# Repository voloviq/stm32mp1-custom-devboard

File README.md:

# stm32mp1-visionsom-custom-devboard
Custom development board for is located in two separated branch for stm32mp1-visionsom from Somlabs and osd32mp1 from Octavo Systems.

Development boards are created in KiCad.

Boards supported with DSI Display with touchscreen, arduino header, power supply, ethernet and usb.

Board 3D View

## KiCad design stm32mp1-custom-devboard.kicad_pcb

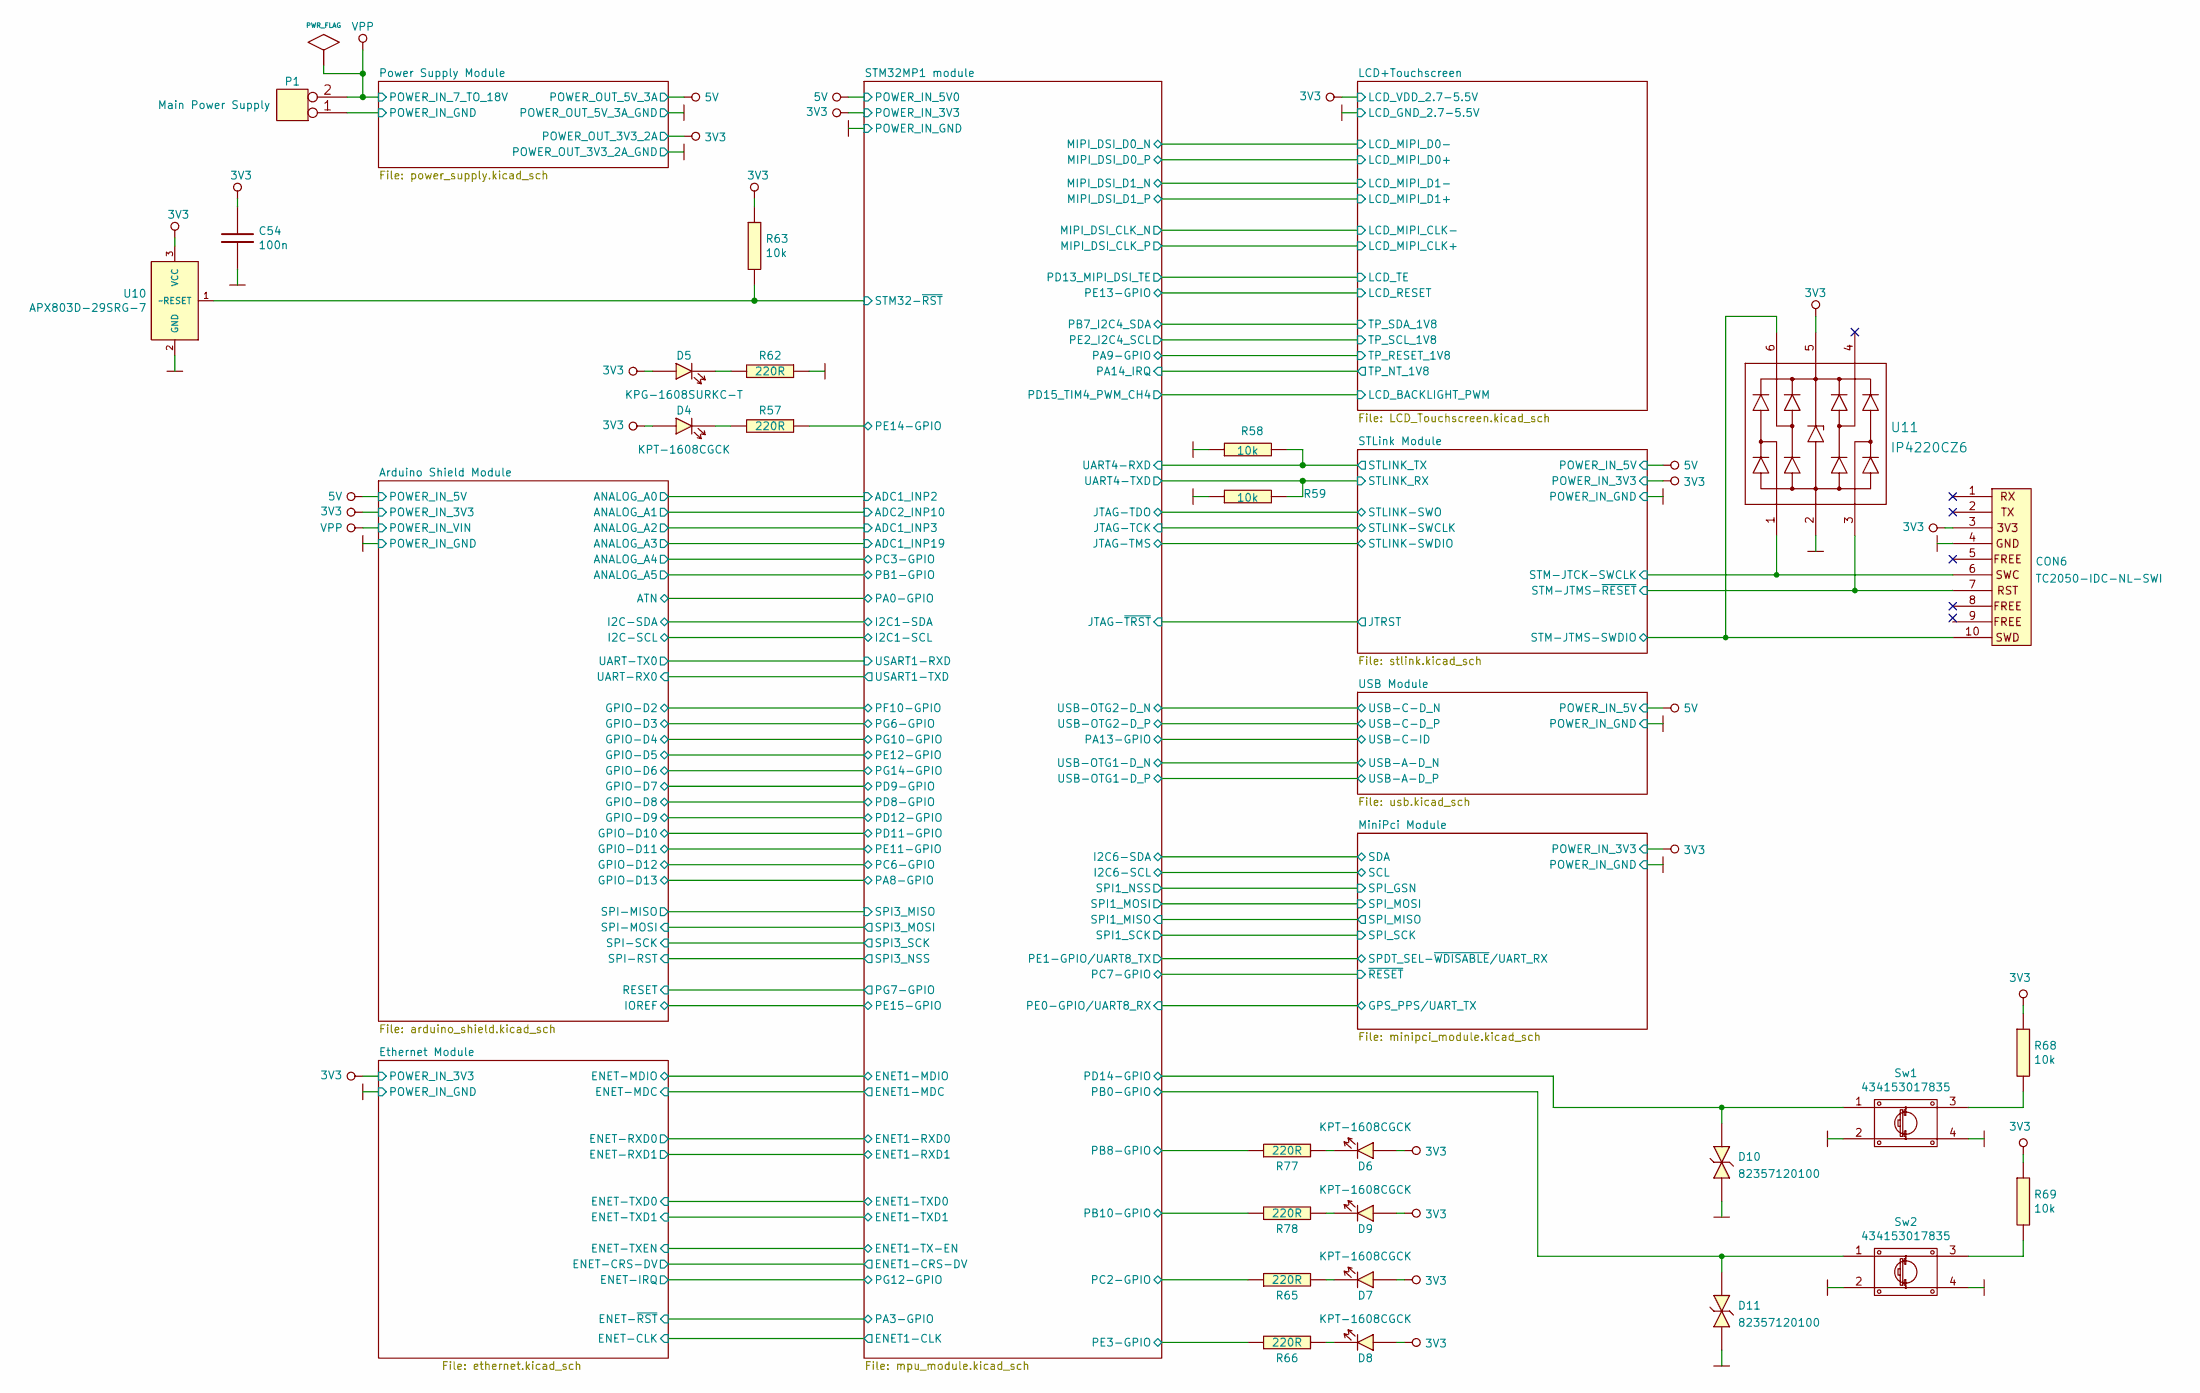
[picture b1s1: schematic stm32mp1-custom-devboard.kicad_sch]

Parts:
C54: 100n; 100nF_0603; Manufacturer Part Number CL10B104JB8NNNC
CON6: TC2050-IDC-NL-SWI; TC2050-IDC-NL
D4, D6, D7, D8, D9: KPT-1608CGCK; LED_KPT-1608CGCK; Manufacturer Part Number KP-1608CGCK; LCSC Part # (optional) C192316
D5: KPG-1608SURKC-T; LED_KPG-1608SURKC-T; Manufacturer Part Number KPG-1608SURKC-T; LCSC Part # (optional) C192315
D10, D11: 82357120100; Manufacturer Part Number 82357120100; LCSC Part #(optional) C39109
P1: Main Power Supply; 2060-452_998-404; Manufacturer Part Number 2060-452/998-404
R57, R62, R65, R66, R77, R78: 220R; 220R_0603; Manufacturer Part Number CQ03SAF2203T5E; LCSC Part #(optional) C103414
R58, R59, R63, R68, R69: 10k; 10k_0603; Manufacturer Part Number 0603SAJ0103T5E
Sw1, Sw2: 434153017835; Manufacturer Part Number 434153017835
U10: APX803D-29SRG-7; Manufacturer Part Number APX803D-29SRG-7; LCSC Part #(optional) C460556
U11: IP4220CZ6; IP4220CZ6_SOT457; Manufacturer Part Number IP4220CZ6.125; LCSC Part #(optional) C2687127

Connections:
3V3: C54.1, CON6.3, D4.1 (A), D5.1 (A), D6.1 (A), D7.1 (A), D8.1 (A), D9.1 (A), R63.1, R68.1, R69.1, U10.3 (VCC), U11.5 (Vp); also elsewhere on the board
/STLink Module/STLINK_RX: R59.2; also elsewhere on the board
/STLink Module/STLINK_TX: R58.2; also elsewhere on the board
/STLink Module/STM-JTCK-SWCLK: CON6.6, U11.1 (I/O1); also elsewhere on the board
/STLink Module/STM-JTMS-SWDIO: CON6.10, U11.6 (I/O4); also elsewhere on the board
/STLink Module/STM-JTMS-~RESET: CON6.7, U11.3 (I/O2); also elsewhere on the board
/STM32MP1 module/PB0-GPIO: D11.2 (K), Sw2.1; also elsewhere on the board
/STM32MP1 module/PB8-GPIO: R77.1; also elsewhere on the board
/STM32MP1 module/PB10-GPIO: R78.1; also elsewhere on the board
/STM32MP1 module/PC2-GPIO: R65.1; also elsewhere on the board
/STM32MP1 module/PD14-GPIO: D10.2 (K), Sw1.1; also elsewhere on the board
/STM32MP1 module/PE3-GPIO: R66.1; also elsewhere on the board
/STM32MP1 module/PE14-GPIO: R57.1; also elsewhere on the board
/STM32MP1 module/STM32-~RST: R63.2, U10.1 (~RESET); also elsewhere on the board
GND: C54.2, CON6.4, D10.1 (A), D11.1 (A), P1.1, R58.1, R59.1, R62.1, Sw1.2, Sw1.4, Sw2.2, Sw2.4, U10.2 (GND), U11.2 (GND); also elsewhere on the board
unnamed: D4.2 (K), R57.2
unnamed: D5.2 (K), R62.2
unnamed: D6.2 (K), R77.2
unnamed: D7.2 (K), R65.2
unnamed: D8.2 (K), R66.2
unnamed: D9.2 (K), R78.2
unnamed: R68.2, Sw1.3
unnamed: R69.2, Sw2.3
VPP: P1.2; also elsewhere on the board

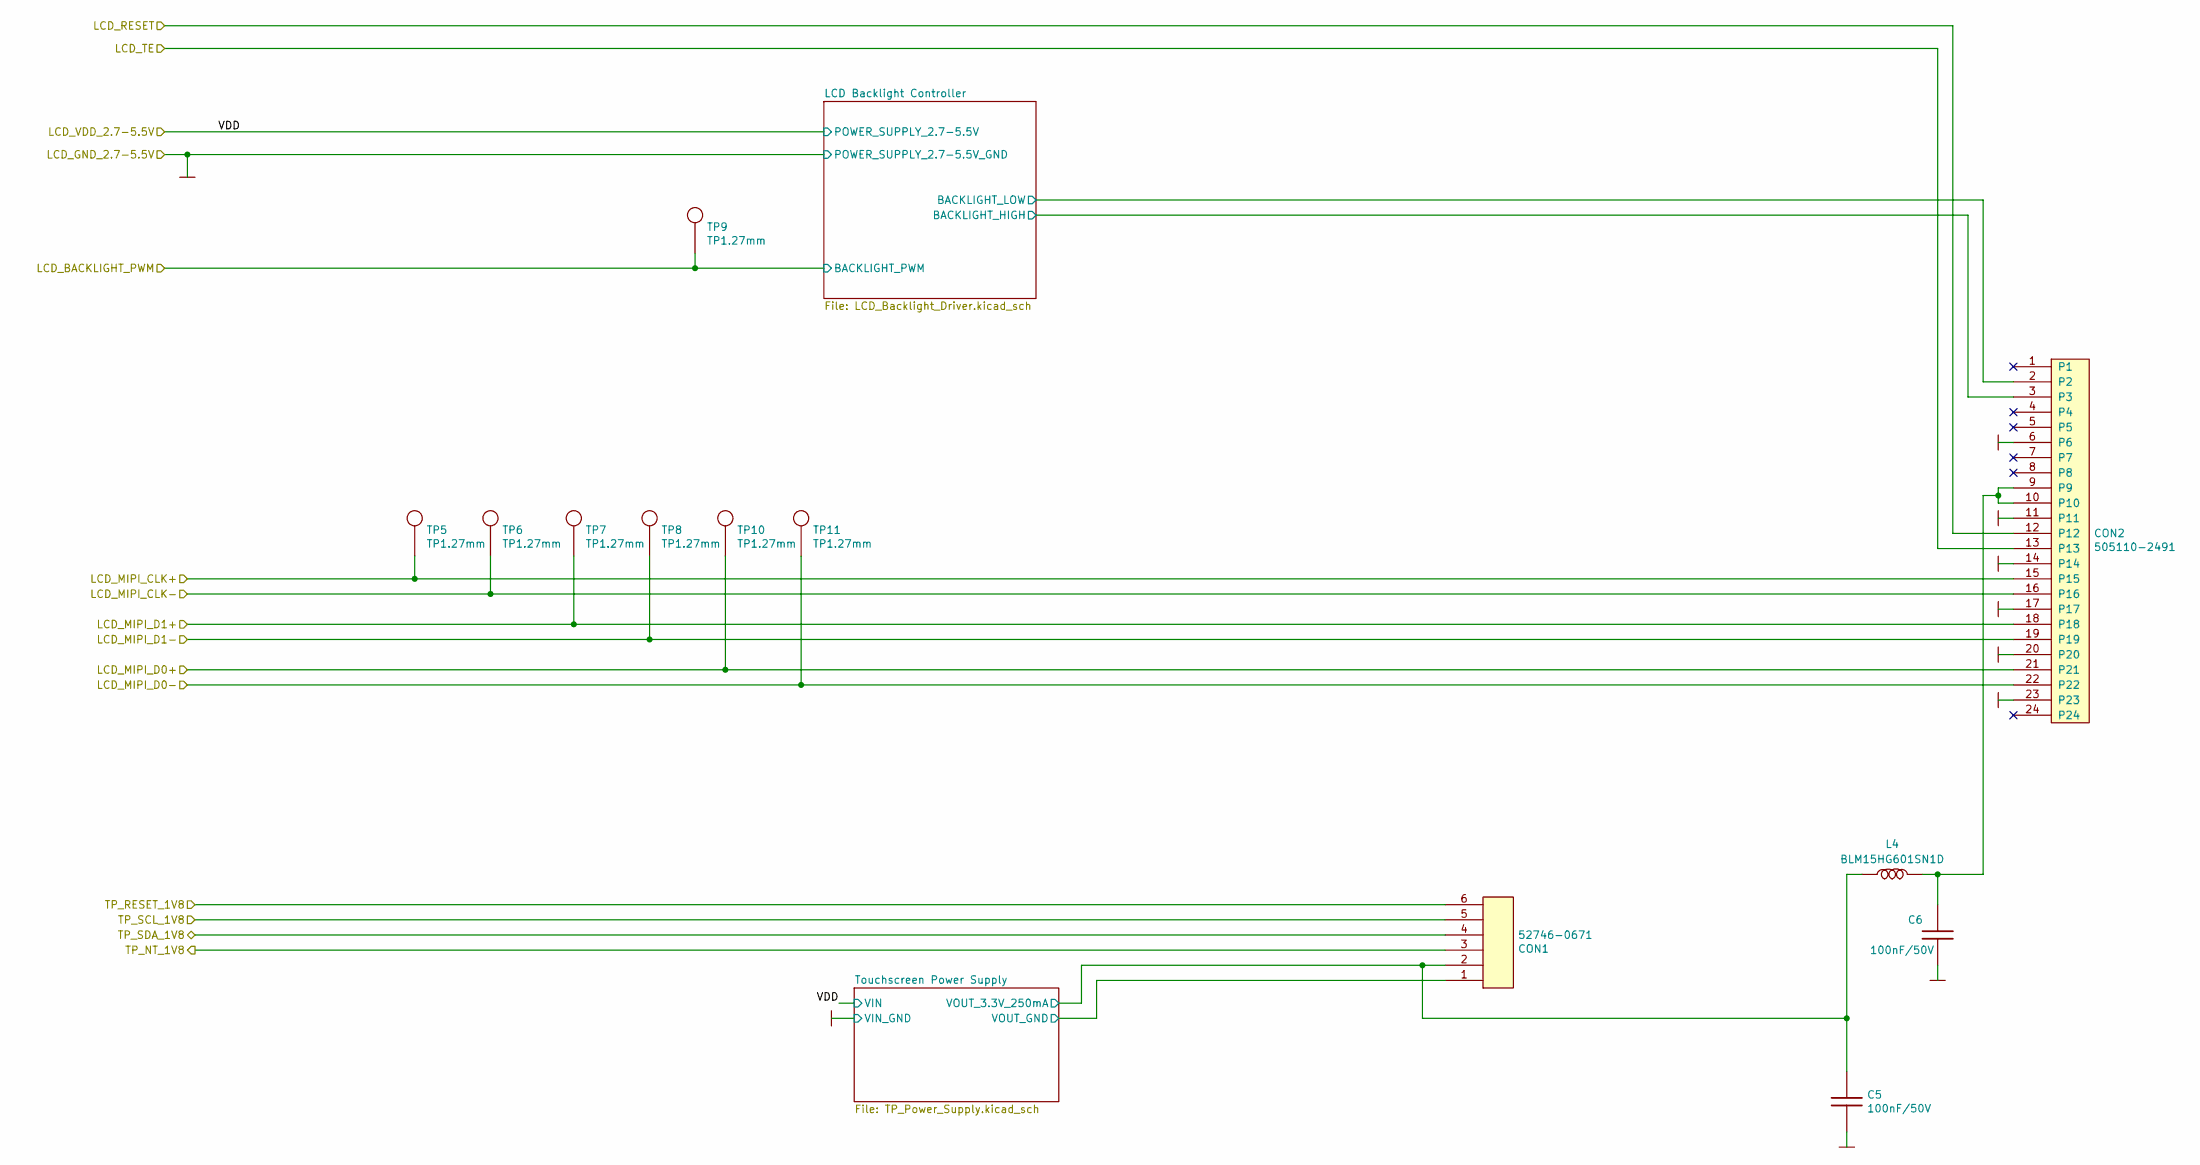
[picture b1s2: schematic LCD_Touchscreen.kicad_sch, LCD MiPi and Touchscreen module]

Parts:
C5, C6: 100nF/50V; 100nF_0603; Manufacturer Part Number CL10B104JB8NNNC
CON1: 52746-0671; Manufacturer Part Number 52746-0671
CON2: 505110-2491; Manufacturer Part Number 505110-2491
L4: BLM15HG601SN1D; BLM15HG601SN1D_0402
TP5, TP6, TP7, TP8, TP9, TP10, TP11: TP1.27mm; Test_Point_1.27mm

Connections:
/LCD+Touchscreen/LCD Backlight Controller/BACKLIGHT_HIGH: CON2.3; also elsewhere on the board
/LCD+Touchscreen/LCD Backlight Controller/BACKLIGHT_LOW: CON2.2; also elsewhere on the board
/LCD+Touchscreen/LCD_BACKLIGHT_PWM: TP9.1 (TP); also elsewhere on the board
/LCD+Touchscreen/LCD_MIPI_CLK+: CON2.15, TP5.1 (TP); also elsewhere on the board
/LCD+Touchscreen/LCD_MIPI_CLK-: CON2.16, TP6.1 (TP); also elsewhere on the board
/LCD+Touchscreen/LCD_MIPI_D0+: CON2.21, TP10.1 (TP); also elsewhere on the board
/LCD+Touchscreen/LCD_MIPI_D0-: CON2.22, TP11.1 (TP); also elsewhere on the board
/LCD+Touchscreen/LCD_MIPI_D1+: CON2.18, TP7.1 (TP); also elsewhere on the board
/LCD+Touchscreen/LCD_MIPI_D1-: CON2.19, TP8.1 (TP); also elsewhere on the board
/LCD+Touchscreen/LCD_RESET: CON2.12; also elsewhere on the board
/LCD+Touchscreen/LCD_TE: CON2.13; also elsewhere on the board
/LCD+Touchscreen/TP_NT_1V8: CON1.3; also elsewhere on the board
/LCD+Touchscreen/TP_RESET_1V8: CON1.6; also elsewhere on the board
/LCD+Touchscreen/TP_SCL_1V8: CON1.5; also elsewhere on the board
/LCD+Touchscreen/TP_SDA_1V8: CON1.4; also elsewhere on the board
/LCD+Touchscreen/Touchscreen Power Supply/VOUT_3.3V_250mA: C5.1, CON1.2, L4.2; also elsewhere on the board
GND: C5.2, C6.2, CON1.1, CON2.6, CON2.11, CON2.14, CON2.17, CON2.20, CON2.23; also elsewhere on the board
unnamed: C6.1, CON2.9, CON2.10, L4.1

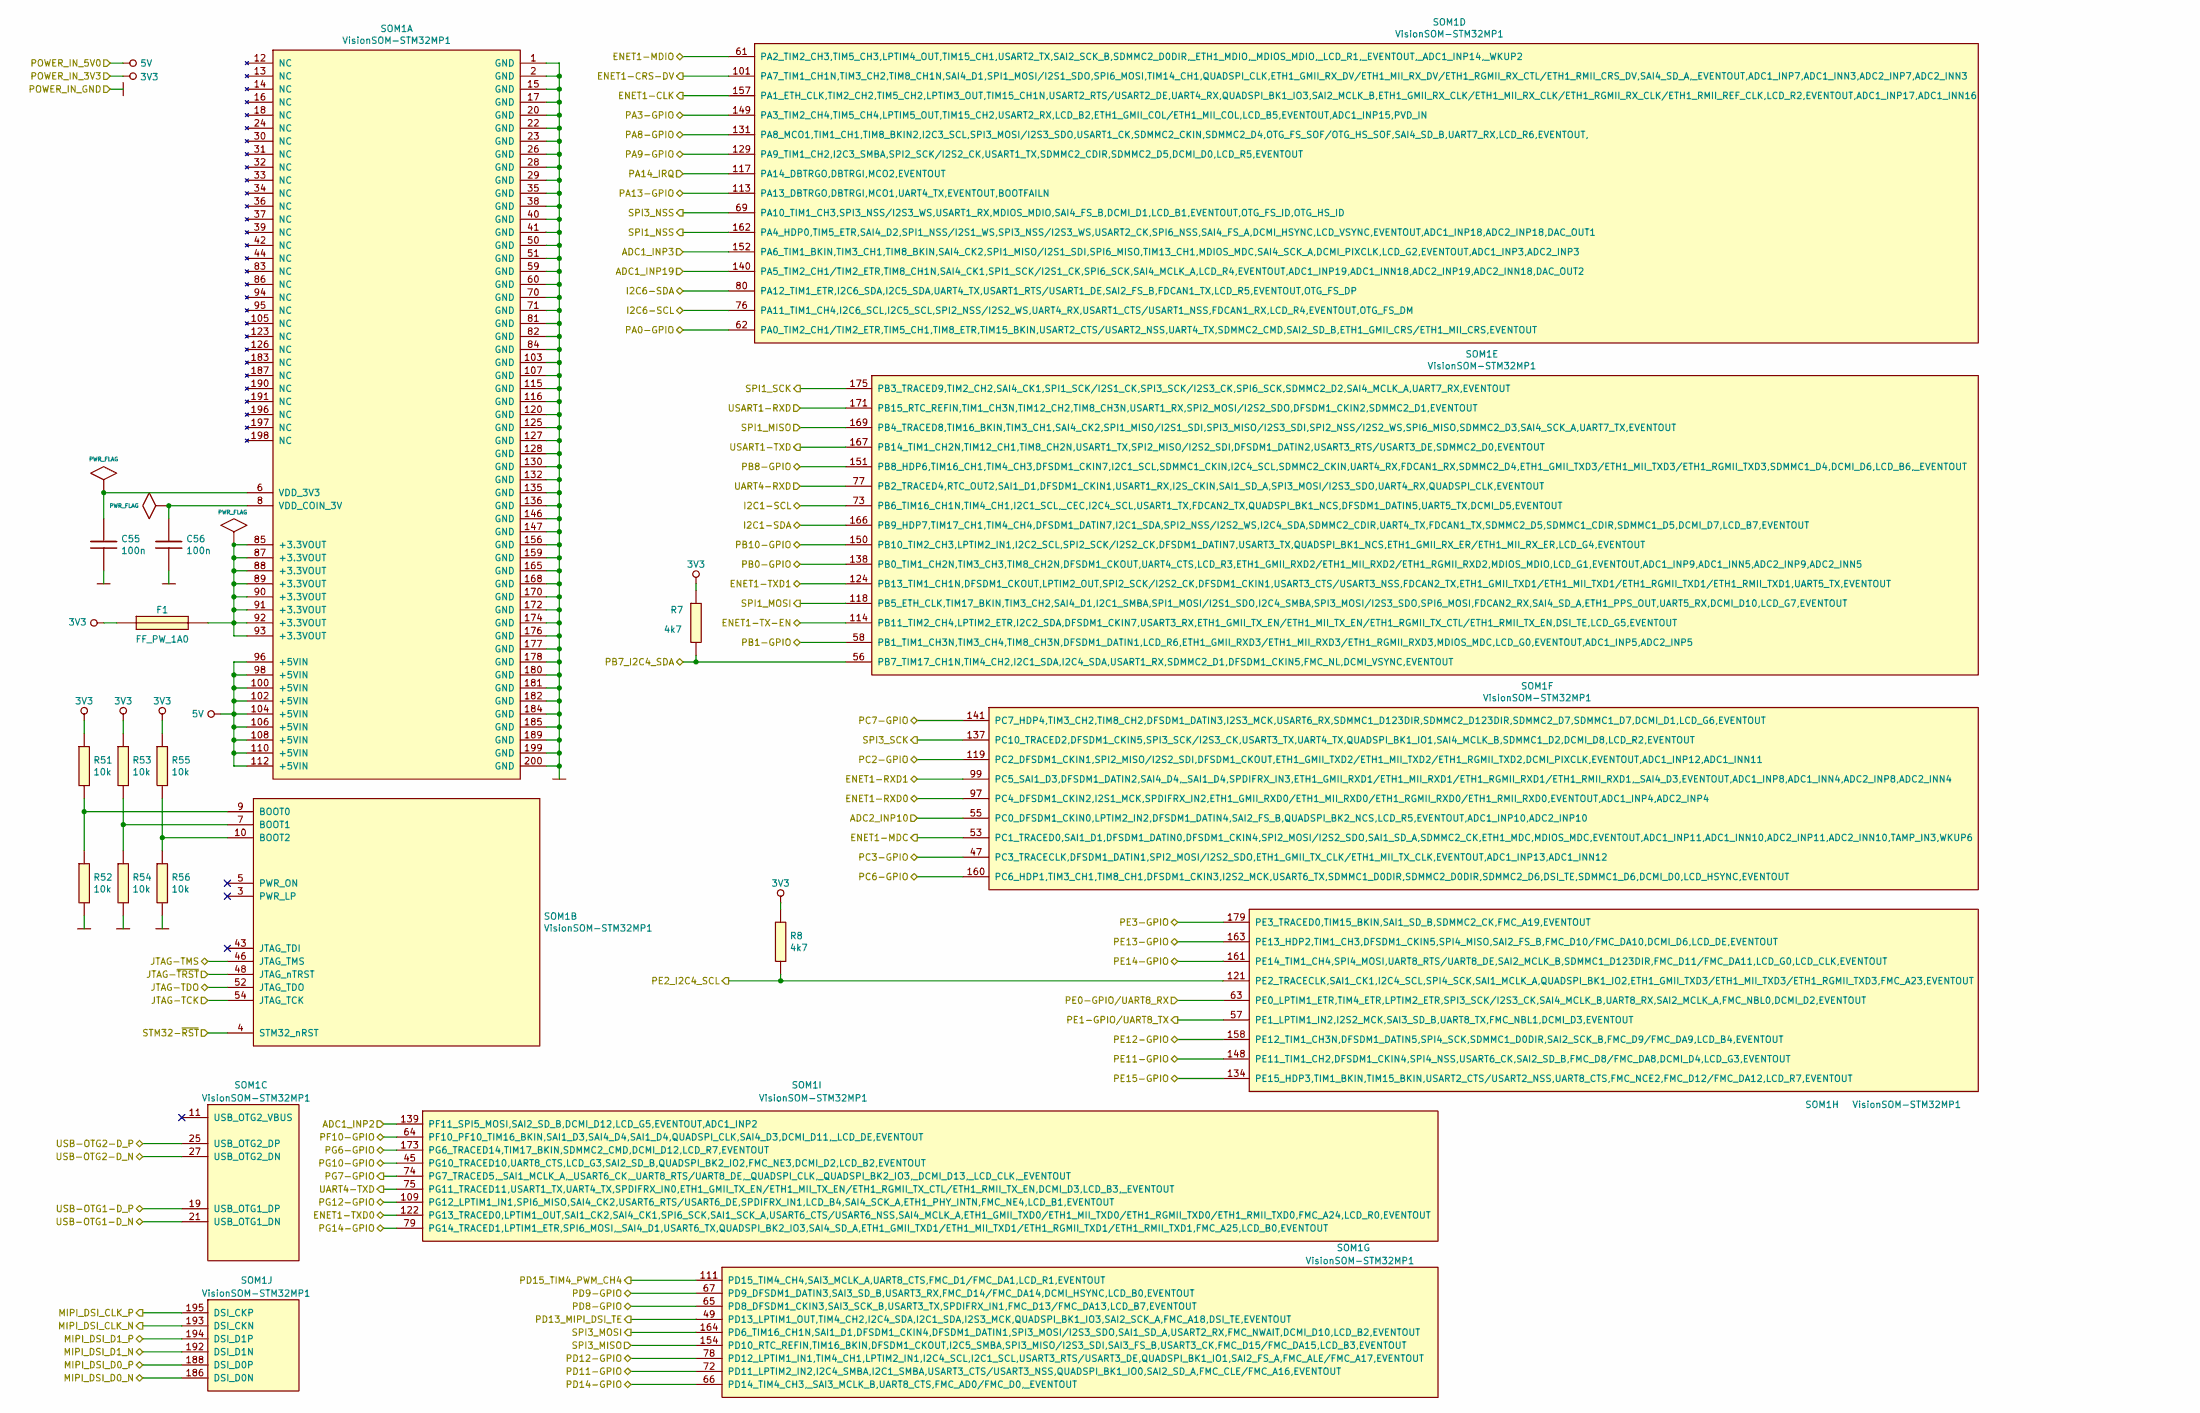
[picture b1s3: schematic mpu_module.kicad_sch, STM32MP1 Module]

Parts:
C55, C56: 100n; 100nF_0603; Manufacturer Part Number CL10B104JB8NNNC
F1: FF_PW_1A0; Fuse_0603-FF_PW_1A0; Manufacturer Part Number FUSE 0603-FF PW 1A
R7, R8: 4k7; 4k7_0603; Manufacturer Part Number 0603SAF4701T5E
R51, R52, R53, R54, R55, R56: 10k; 10k_0603; Manufacturer Part Number 0603SAJ0103T5E
SOM1: VisionSOM-STM32MP1; Manufacturer Part Number VisionSOM-STM32MP1

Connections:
3V3: F1.1, R7.1, R8.1, R51.1, R53.1, R55.1; also elsewhere on the board
5V: SOM1.96 (+5VIN), SOM1.98 (+5VIN), SOM1.100 (+5VIN), SOM1.102 (+5VIN), SOM1.104 (+5VIN), SOM1.106 (+5VIN), SOM1.108 (+5VIN), SOM1.110 (+5VIN), SOM1.112 (+5VIN); also elsewhere on the board
/Arduino Shield Module/ANALOG_A0: SOM1.139 (PF11_SPI5_MOSI,SAI2_SD_B,DCMI_D12,LCD_G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); also elsewhere on the board
/Arduino Shield Module/ANALOG_A1: SOM1.55 (PC0_DFSDM1_CKIN0,LPTIM2_IN2,DFSDM1_DATI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); also elsewhere on the board
/Arduino Shield Module/ANALOG_A2: SOM1.152 (PA6_TIM1_BKIN,TIM3_CH1,TIM8_BKIN,SAI4_C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); also elsewhere on the board
/Arduino Shield Module/ANALOG_A3: SOM1.140 (PA5_TIM2_CH1/TIM2_ETR,TIM8_CH1N,SAI4_CK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); also elsewhere on the board
/Arduino Shield Module/ANALOG_A4: SOM1.47 (PC3_TRACECLK,DFSDM1_DATIN1,SPI2_MOSI/I2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); also elsewhere on the board
/Arduino Shield Module/ANALOG_A5: SOM1.58 (PB1_TIM1_CH3N,TIM3_CH4,TIM8_CH3N,DFSDM1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); also elsewhere on the board
/Arduino Shield Module/ATN: SOM1.62 (PA0_TIM2_CH1/TIM2_ETR,TIM5_CH1,TIM8_ETR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); also elsewhere on the board
/Arduino Shield Module/GPIO-D2: SOM1.64 (PF10_PF10_TIM16_BKIN,SAI1_D3,SAI4_D4,SA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); also elsewhere on the board
/Arduino Shield Module/GPIO-D3: SOM1.173 (PG6_TRACED14,TIM17_BKIN,SDMMC2_CMD,DCMI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); also elsewhere on the board
/Arduino Shield Module/GPIO-D4: SOM1.45 (PG10_TRACED10,UART8_CTS,LCD_G3,SAI2_SD_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); also elsewhere on the board
/Arduino Shield Module/GPIO-D5: SOM1.158 (PE12_TIM1_CH3N,DFSDM1_DATIN5,SPI4_SCK,S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); also elsewhere on the board
/Arduino Shield Module/GPIO-D6: SOM1.79 (PG14_TRACED1,LPTIM1_ETR,SPI6_MOSI,_SAI4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); also elsewhere on the board
/Arduino Shield Module/GPIO-D7: SOM1.67 (PD9_DFSDM1_DATIN3,SAI3_SD_B,USART3_RX,F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); also elsewhere on the board
/Arduino Shield Module/GPIO-D8: SOM1.65 (PD8_DFSDM1_CKIN3,SAI3_SCK_B,USART3_TX,S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); also elsewhere on the board
/Arduino Shield Module/GPIO-D9: SOM1.78 (PD12_LPTIM1_IN1,TIM4_CH1,LPTIM2_IN1,I2C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); also elsewhere on the board
/Arduino Shield Module/GPIO-D10: SOM1.72 (PD11_LPTIM2_IN2,I2C4_SMBA,I2C1_SMBA,USA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); also elsewhere on the board
/Arduino Shield Module/GPIO-D11: SOM1.148 (PE11_TIM1_CH2,DFSDM1_CKIN4,SPI4_NSS,USA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); also elsewhere on the board
/Arduino Shield Module/GPIO-D12: SOM1.160 (PC6_HDP1,TIM3_CH1,TIM8_CH1,DFSDM1_CKIN3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); also elsewhere on the board
/Arduino Shield Module/GPIO-D13: SOM1.131 (PA8_MCO1,TIM1_CH1,TIM8_BKIN2,I2C3_SCL,S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); also elsewhere on the board
/Arduino Shield Module/I2C-SCL: SOM1.73 (PB6_TIM16_CH1N,TIM4_CH1,I2C1_SCL,_CEC,I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); also elsewhere on the board
/Arduino Shield Module/I2C-SDA: SOM1.166 (PB9_HDP7,TIM17_CH1,TIM4_CH4,DFSDM1_DATI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); also elsewhere on the board
/Arduino Shield Module/IOREF: SOM1.134 (PE15_HDP3,TIM1_BKIN,TIM15_BKIN,USART2_C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); also elsewhere on the board
/Arduino Shield Module/RESET: SOM1.74 (PG7_TRACED5,_SAI1_MCLK_A,_USART6_CK,_UA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); also elsewhere on the board
/Arduino Shield Module/SPI-MISO: SOM1.154 (PD10_RTC_REFIN,TIM16_BKIN,DFSDM1_CKOUT,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); also elsewhere on the board
/Arduino Shield Module/SPI-MOSI: SOM1.164 (PD6_TIM16_CH1N,SAI1_D1,DFSDM1_CKIN4,DFS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); also elsewhere on the board
/Arduino Shield Module/SPI-RST: SOM1.69 (PA10_TIM1_CH3,SPI3_NSS/I2S3_WS,USART1_R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); also elsewhere on the board
/Arduino Shield Module/SPI-SCK: SOM1.137 (PC10_TRACED2,DFSDM1_CKIN5,SPI3_SCK/I2S3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); also elsewhere on the board
/Arduino Shield Module/UART-RX0: SOM1.167 (PB14_TIM1_CH2N,TIM12_CH1,TIM8_CH2N,USAR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); also elsewhere on the board
/Arduino Shield Module/UART-TX0: SOM1.171 (PB15_RTC_REFIN,TIM1_CH3N,TIM12_CH2,TIM8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); also elsewhere on the board
/Ethernet Module/ENET-CLK: SOM1.157 (PA1_ETH_CLK,TIM2_CH2,TIM5_CH2,LPTIM3_OU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); also elsewhere on the board
/Ethernet Module/ENET-CRS-DV: SOM1.101 (PA7_TIM1_CH1N,TIM3_CH2,TIM8_CH1N,SAI4_D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); also elsewhere on the board
/Ethernet Module/ENET-IRQ: SOM1.109 (PG12_LPTIM1_IN1,SPI6_MISO,SAI4_CK2,USAR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); also elsewhere on the board
/Ethernet Module/ENET-MDC: SOM1.53 (PC1_TRACED0,SAI1_D1,DFSDM1_DATIN0,DFSDM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); also elsewhere on the board
/Ethernet Module/ENET-MDIO: SOM1.61 (PA2_TIM2_CH3,TIM5_CH3,LPTIM4_OUT,TIM15_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); also elsewhere on the board
/Ethernet Module/ENET-RXD0: SOM1.97 (PC4_DFSDM1_CKIN2,I2S1_MCK,SPDIFRX_IN2,E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); also elsewhere on the board
/Ethernet Module/ENET-RXD1: SOM1.99 (PC5_SAI1_D3,DFSDM1_DATIN2,SAI4_D4,_SAI1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); also elsewhere on the board
/Ethernet Module/ENET-TXD0: SOM1.122 (PG13_TRACED0,LPTIM1_OUT,SAI1_CK2,SAI4_C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); also elsewhere on the board
/Ethernet Module/ENET-TXD1: SOM1.124 (PB13_TIM1_CH1N,DFSDM1_CKOUT,LPTIM2_OUT,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); also elsewhere on the board
/Ethernet Module/ENET-TXEN: SOM1.114 (PB11_TIM2_CH4,LPTIM2_ETR,I2C2_SDA,DFSDM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); also elsewhere on the board
/Ethernet Module/ENET-~RST: SOM1.149 (PA3_TIM2_CH4,TIM5_CH4,LPTIM5_OUT,TIM15_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); also elsewhere on the board
/LCD+Touchscreen/LCD_BACKLIGHT_PWM: SOM1.111 (PD15_TIM4_CH4,SAI3_MCLK_A,UART8_CTS,FMC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); also elsewhere on the board
/LCD+Touchscreen/LCD_MIPI_CLK+: SOM1.195 (DSI_CKP); also elsewhere on the board
/LCD+Touchscreen/LCD_MIPI_CLK-: SOM1.193 (DSI_CKN); also elsewhere on the board
/LCD+Touchscreen/LCD_MIPI_D0+: SOM1.188 (DSI_D0P); also elsewhere on the board
/LCD+Touchscreen/LCD_MIPI_D0-: SOM1.186 (DSI_D0N); also elsewhere on the board
/LCD+Touchscreen/LCD_MIPI_D1+: SOM1.194 (DSI_D1P); also elsewhere on the board
/LCD+Touchscreen/LCD_MIPI_D1-: SOM1.192 (DSI_D1N); also elsewhere on the board
/LCD+Touchscreen/LCD_RESET: SOM1.163 (PE13_HDP2,TIM1_CH3,DFSDM1_CKIN5,SPI4_MI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); also elsewhere on the board
/LCD+Touchscreen/LCD_TE: SOM1.49 (PD13_LPTIM1_OUT,TIM4_CH2,I2C4_SDA,I2C1_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); also elsewhere on the board
/LCD+Touchscreen/TP_NT_1V8: SOM1.117 (PA14_DBTRGO,DBTRGI,MCO2,EVENTOUT); also elsewhere on the board
/LCD+Touchscreen/TP_RESET_1V8: SOM1.129 (PA9_TIM1_CH2,I2C3_SMBA,SPI2_SCK/I2S2_CK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); also elsewhere on the board
/LCD+Touchscreen/TP_SCL_1V8: R8.2, SOM1.121 (PE2_TRACECLK,SAI1_CK1,I2C4_SCL,SPI4_SCK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); also elsewhere on the board
/LCD+Touchscreen/TP_SDA_1V8: R7.2, SOM1.56 (PB7_TIM17_CH1N,TIM4_CH2,I2C1_SDA,I2C4_S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); also elsewhere on the board
/MiniPci Module/GPS_PPS/UART_TX: SOM1.63 (PE0_LPTIM1_ETR,TIM4_ETR,LPTIM2_ETR,SPI3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); also elsewhere on the board
/MiniPci Module/SCL: SOM1.76 (PA11_TIM1_CH4,I2C6_SCL,I2C5_SCL,SPI2_NS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); also elsewhere on the board
/MiniPci Module/SDA: SOM1.80 (PA12_TIM1_ETR,I2C6_SDA,I2C5_SDA,UART4_T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); also elsewhere on the board
/MiniPci Module/SPDT_SEL-~WDISABLE/UART_RX: SOM1.57 (PE1_LPTIM1_IN2,I2S2_MCK,SAI3_SD_B,UART8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); also elsewhere on the board
/MiniPci Module/SPI_GSN: SOM1.162 (PA4_HDP0,TIM5_ETR,SAI4_D2,SPI1_NSS/I2S1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); also elsewhere on the board
/MiniPci Module/SPI_MISO: SOM1.169 (PB4_TRACED8,TIM16_BKIN,TIM3_CH1,SAI4_CK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); also elsewhere on the board
/MiniPci Module/SPI_MOSI: SOM1.118 (PB5_ETH_CLK,TIM17_BKIN,TIM3_CH2,SAI4_D1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); also elsewhere on the board
/MiniPci Module/SPI_SCK: SOM1.175 (PB3_TRACED9,TIM2_CH2,SAI4_CK1,SPI1_SCK/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); also elsewhere on the board
/MiniPci Module/~RESET: SOM1.141 (PC7_HDP4,TIM3_CH2,TIM8_CH2,DFSDM1_DATIN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); also elsewhere on the board
/STLink Module/JTRST: SOM1.48 (JTAG_nTRST); also elsewhere on the board
/STLink Module/STLINK-SWCLK: SOM1.54 (JTAG_TCK); also elsewhere on the board
/STLink Module/STLINK-SWDIO: SOM1.46 (JTAG_TMS); also elsewhere on the board
/STLink Module/STLINK-SWO: SOM1.52 (JTAG_TDO); also elsewhere on the board
/STLink Module/STLINK_RX: SOM1.75 (PG11_TRACED11,USART1_TX,UART4_TX,SPDIFR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); also elsewhere on the board
/STLink Module/STLINK_TX: SOM1.77 (PB2_TRACED4,RTC_OUT2,SAI1_D1,DFSDM1_CKI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); also elsewhere on the board
/STM32MP1 module/PA13-GPIO: SOM1.113 (PA13_DBTRGO,DBTRGI,MCO1,UART4_TX,EVENTO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); also elsewhere on the board
/STM32MP1 module/PB0-GPIO: SOM1.138 (PB0_TIM1_CH2N,TIM3_CH3,TIM8_CH2N,DFSDM1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); also elsewhere on the board
/STM32MP1 module/PB8-GPIO: SOM1.151 (PB8_HDP6,TIM16_CH1,TIM4_CH3,DFSDM1_CKIN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); also elsewhere on the board
/STM32MP1 module/PB10-GPIO: SOM1.150 (PB10_TIM2_CH3,LPTIM2_IN1,I2C2_SCL,SPI2_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); also elsewhere on the board
/STM32MP1 module/PC2-GPIO: SOM1.119 (PC2_DFSDM1_CKIN1,SPI2_MISO/I2S2_SDI,DFS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); also elsewhere on the board
/STM32MP1 module/PD14-GPIO: SOM1.66 (PD14_TIM4_CH3,_SAI3_MCLK_B,UART8_CTS,FM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); also elsewhere on the board
/STM32MP1 module/PE3-GPIO: SOM1.179 (PE3_TRACED0,TIM15_BKIN,SAI1_SD_B,SDMMC2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); also elsewhere on the board
/STM32MP1 module/PE14-GPIO: SOM1.161 (PE14_TIM1_CH4,SPI4_MOSI,UART8_RTS/UART8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); also elsewhere on the board
/STM32MP1 module/STM32-~RST: SOM1.4 (STM32_nRST); also elsewhere on the board
/STM32MP1 module/USB-OTG1-D_N: SOM1.21 (USB_OTG1_DN); also elsewhere on the board
/STM32MP1 module/USB-OTG1-D_P: SOM1.19 (USB_OTG1_DP); also elsewhere on the board
/STM32MP1 module/USB-OTG2-D_N: SOM1.27 (USB_OTG2_DN); also elsewhere on the board
/STM32MP1 module/USB-OTG2-D_P: SOM1.25 (USB_OTG2_DP); also elsewhere on the board
GND: C55.2, C56.2, R52.2, R54.2, R56.2, SOM1.1 (GND), SOM1.2 (GND), SOM1.15 (GND), SOM1.17 (GND), SOM1.20 (GND), SOM1.22 (GND), SOM1.23 (GND), SOM1.26 (GND), SOM1.28 (GND), SOM1.29 (GND), SOM1.35 (GND), SOM1.38 (GND), SOM1.40 (GND), SOM1.41 (GND), SOM1.50 (GND), SOM1.51 (GND), SOM1.59 (GND), SOM1.60 (GND), SOM1.70 (GND), SOM1.71 (GND), SOM1.81 (GND), SOM1.82 (GND), SOM1.84 (GND), SOM1.103 (GND), SOM1.107 (GND), SOM1.115 (GND), SOM1.116 (GND), SOM1.120 (GND), SOM1.125 (GND), SOM1.127 (GND), SOM1.128 (GND), SOM1.130 (GND), SOM1.132 (GND), SOM1.135 (GND), SOM1.136 (GND), SOM1.146 (GND), SOM1.147 (GND), SOM1.156 (GND), SOM1.159 (GND), SOM1.165 (GND), SOM1.168 (GND), SOM1.170 (GND), SOM1.172 (GND), SOM1.174 (GND), SOM1.176 (GND), SOM1.177 (GND), SOM1.178 (GND), SOM1.180 (GND), SOM1.181 (GND), SOM1.182 (GND), SOM1.184 (GND), SOM1.185 (GND), SOM1.189 (GND), SOM1.199 (GND), SOM1.200 (GND); also elsewhere on the board
unnamed: C55.1, SOM1.6 (VDD_3V3)
unnamed: C56.1, SOM1.8 (VDD_COIN_3V)
unnamed: F1.2, SOM1.85 (+3.3VOUT), SOM1.87 (+3.3VOUT), SOM1.88 (+3.3VOUT), SOM1.89 (+3.3VOUT), SOM1.90 (+3.3VOUT), SOM1.91 (+3.3VOUT), SOM1.92 (+3.3VOUT), SOM1.93 (+3.3VOUT)
unnamed: R51.2, R52.1, SOM1.9 (BOOT0)
unnamed: R53.2, R54.1, SOM1.7 (BOOT1)
unnamed: R55.2, R56.1, SOM1.10 (BOOT2)

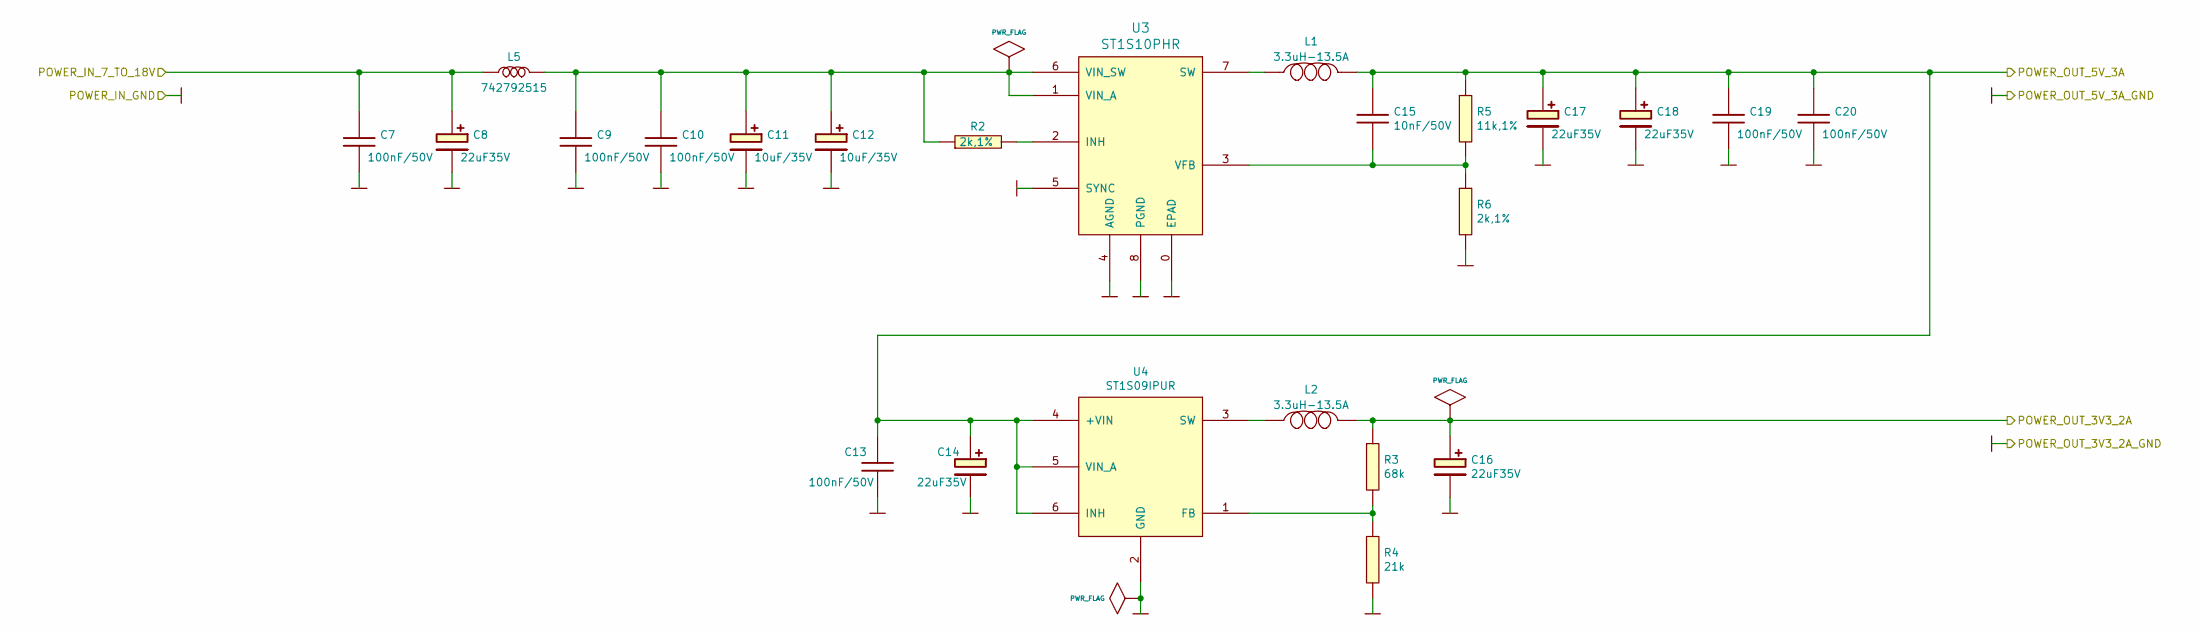
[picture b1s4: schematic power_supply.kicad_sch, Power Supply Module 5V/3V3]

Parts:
C7, C9, C10, C13, C19, C20: 100nF/50V; 100nF_0603; Manufacturer Part Number CL10B104JB8NNNC
C8, C14, C16, C17, C18: 22uF35V; 22uF_35V_Size_D; Manufacturer Part Number 293D226X9035D2TE3; LCSC Part # (optional) C126947
C11, C12: 10uF/35V; 10uF_35V_C; Manufacturer Part Number 293D106X9035C2TE3; LCSC Part # (optional) C169217
C15: 10nF/50V; 10nF_0603; Manufacturer Part Number VJ0603Y103KXAPW1BC; LCSC Part # (optional) C342901
L1, L2: 3.3uH-13.5A; ASPI-0630HI-3R3M-T15; Manufacturer Part Number ASPI-0630HI-3R3M-T15
L5: 742792515; Manufacturer Part Number 742792515; LCSC Part #(optional) C350947
R2, R6: 2k,1%; 2k_0603; Manufacturer Part Number CQ03SAF2001T5E; LCSC Part #(optional) C234435
R3: 68k; 68k_0603; Manufacturer Part Number 0603SAF6802T5E; LCSC Part #(optional) C160055
R4: 21k; 21k_0603; Manufacturer Part Number 0603SAF2102T5E; LCSC Part #(optional) C177529
R5: 11k,1%; 11k_0603; Manufacturer Part Number 0603SAF1102T5E
U3: ST1S10PHR; ST1S10PHR_SOIC8; Manufacturer Part Number ST1S10PHR; LCSC Part #(optional) C11175
U4: ST1S09IPUR; Manufacturer Part Number ST1S09IPUR; LCSC Part #(optional) C361028

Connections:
3V3: C16.1, L2.2, R3.1; also elsewhere on the board
5V: C13.1, C14.1, C15.1, C17.1, C18.1, C19.1, C20.1, L1.2, R5.1, U4.4 (+VIN), U4.5 (VIN_A), U4.6 (INH); also elsewhere on the board
GND: C7.2, C8.2, C9.2, C10.2, C11.2, C12.2, C13.2, C14.2, C16.2, C17.2, C18.2, C19.2, C20.2, R4.2, R6.2, U3.0 (EPAD), U3.4 (AGND), U3.5 (SYNC), U3.8 (PGND), U4.2 (GND); also elsewhere on the board
unnamed: C9.1, C10.1, C11.1, C12.1, L5.2, R2.1, U3.1 (VIN_A), U3.6 (VIN_SW)
unnamed: C15.2, R5.2, R6.1, U3.3 (VFB)
unnamed: L1.1, U3.7 (SW)
unnamed: L2.1, U4.3 (SW)
unnamed: R2.2, U3.2 (INH)
unnamed: R3.2, R4.1, U4.1 (FB)
VPP: C7.1, C8.1, L5.1; also elsewhere on the board
